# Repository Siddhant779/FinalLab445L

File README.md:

# ECE445L Final Lab
## Link to award won - Spring 2024
https://github.com/ECE445L/ECE445L-Winners
## Deliverables

The deliverables folder should contain documentation about your project as
outlined in the lab documents.

## HW

The hw folder should contain your schematic and board files for your PCB or
circuits. In labs 3-11, you will be creating schematics for your circuit
in EAGLE. A setup tutorial can be found
[here](https://www.shawnvictor.net/autodesk-eagle.html).

## SW

The sw folder should contain your application firmware and software written for
the lab. The sw/inc folder contains firmware drivers written for you by
Professor Valvano. Feel free to write your own (in fact, in some labs, you may
be required to write your own).

You can place any other source files in the sw/ folder. TAs will look at the
files you create and/or modify for software quality and for running your
project.

## Resources

A couple files are provided in the Resources folder so you don't have to keep
searching for that one TI document. Some of them are immediately useful, like
the TM4C datasheet. Others may be useful for your final project, like the
TM4C_System_Design_Guidelines page.

## Git and Github

We will extensively use Git and Github for managing lab projects. This makes it
easier for TAs to grade and help debug the project by allowing the students to
see commit histories, maintain a common project structure, collaborate with
partners, merge different codebases, and to debug work.

Two common ways of using Git and Github are [Github Desktop](https://desktop.github.com/) and the [command line](https://git-scm.com/downloads). [Tutorials](https://dev.to/mollynem/git-github--workflow-fundamentals-5496) are also abundant on the net for you to peruse. We've provided a cheatsheet for git in the Resources folder.

It is highly recommended to make the most out of Git, even if you've never used
it before. Version control will save you a lot of suffering, and tools like Git
or SVN are ubiquitous in the industry.

## Lab Report

Following the lab doc provided at the root of this project, the TAs request you
submit a lab report in Microsoft Word (or Pages, if you're a Mac user). Please
name it `EID_lab_LAB_NUMBER_report.pdf`. Templates are provided in the root dir.

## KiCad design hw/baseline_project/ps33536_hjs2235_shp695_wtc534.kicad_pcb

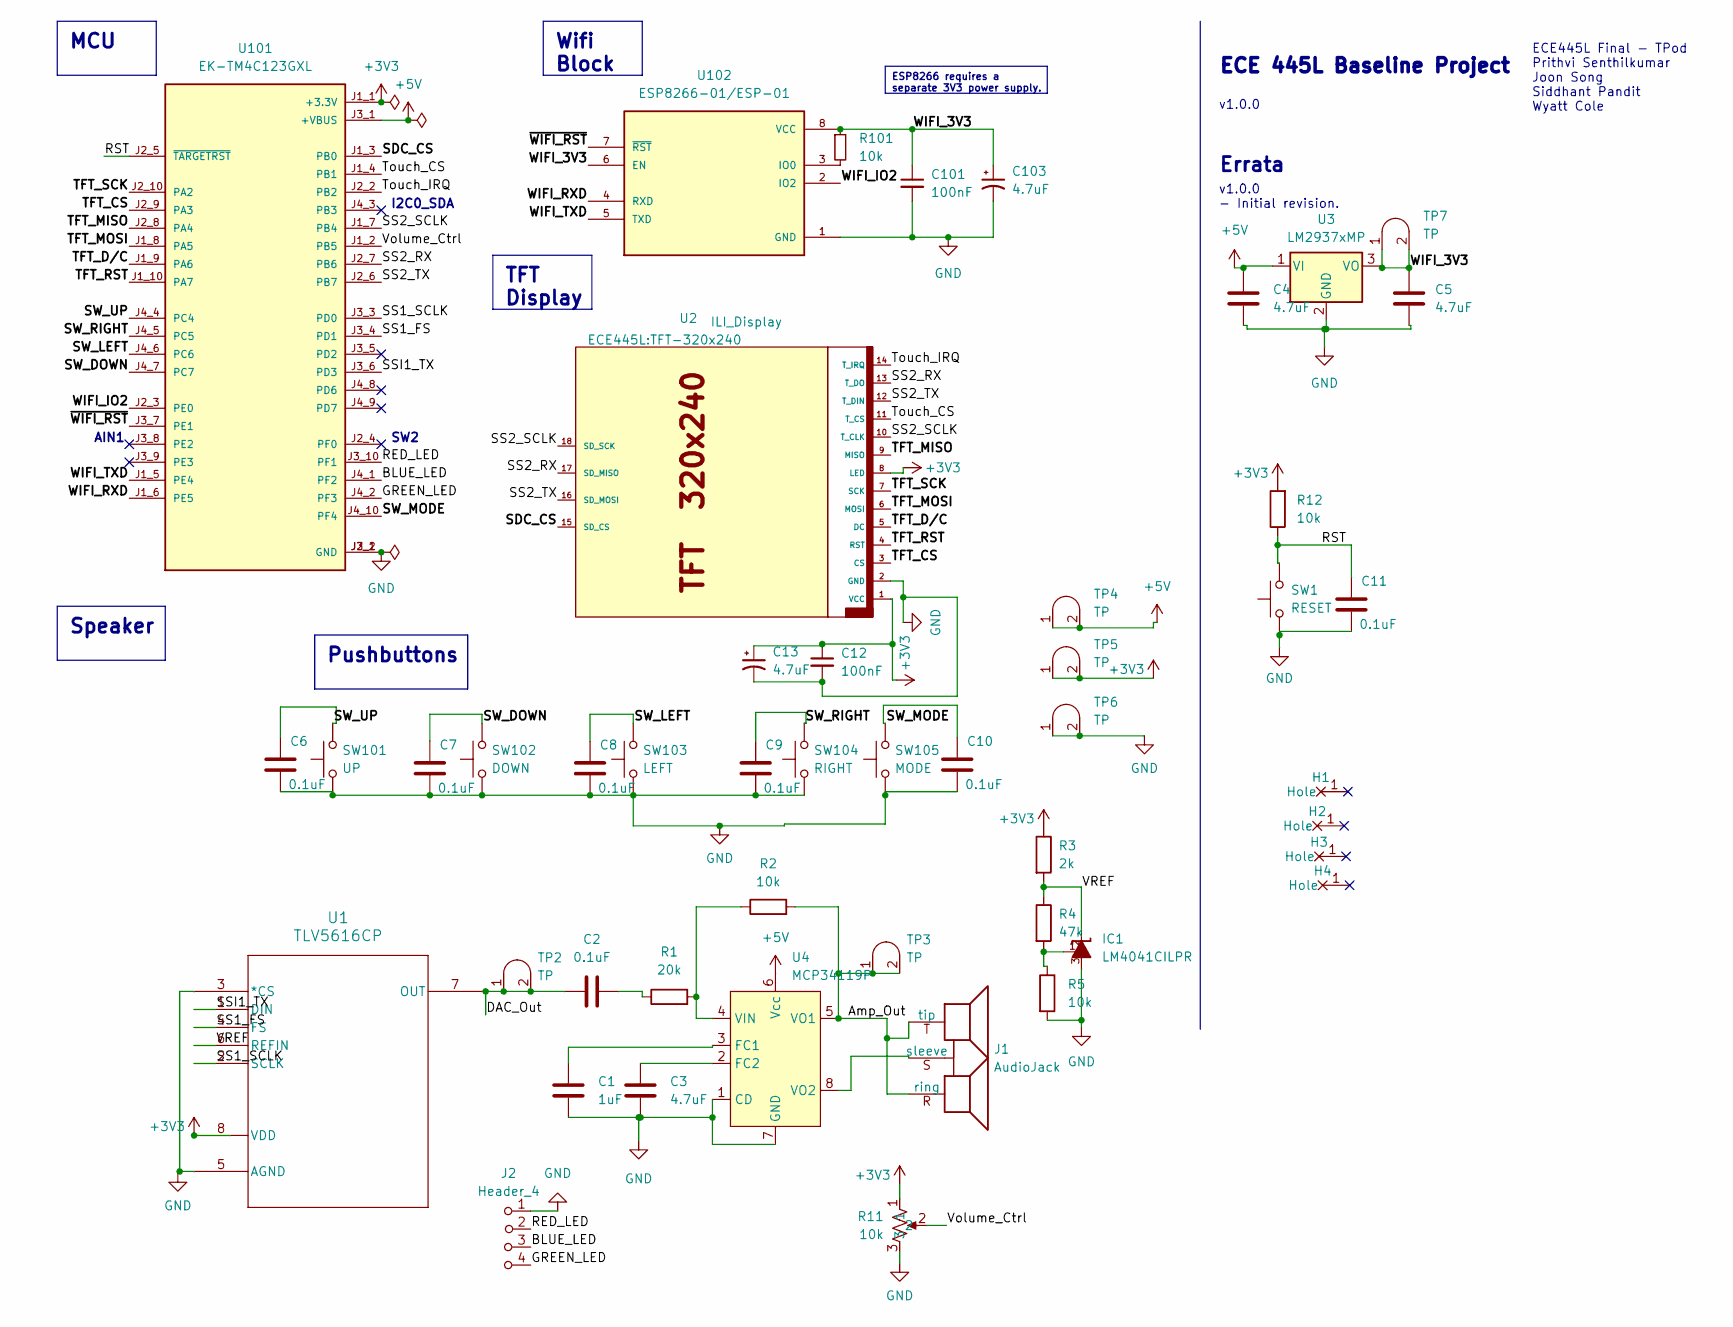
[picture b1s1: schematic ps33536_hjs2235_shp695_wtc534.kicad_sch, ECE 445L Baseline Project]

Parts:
C1: 1uF; C_Axial_200mil
C2, C6, C7, C8, C9, C10, C11: 0.1uF; C_Axial_200mil
C3, C4, C5: 4.7uF; C_Axial_200mil
C12, C101: 100nF; C_Axial_200mil
C13, C103: 4.7uF; CP_Radial_Tantal200mil
H1, H2, H3, H4: MountingHole_4_40
IC1: LM4041CILPR; ti_LM4041CILPR
J1: AudioJack; Jack_3.5mm_CUI_SJ1-3523N_Horizontal
J2: Header_4; PinHeader_1x04_P2.54mm_Vertical
R1: 20k; R_Axial_DIN0207_L6.3mm_D2.5mm_P10.16mm_Horizontal
R2, R5, R12, R101: 10k; R_Axial_DIN0207_L6.3mm_D2.5mm_P10.16mm_Horizontal
R3: 2k; R_Axial_DIN0207_L6.3mm_D2.5mm_P10.16mm_Horizontal
R4: 47k; R_Axial_DIN0207_L6.3mm_D2.5mm_P10.16mm_Horizontal
R11: 10k; Potentiometer
SW1: RESET; SW_PUSH_6mm
SW101: UP; SW_PUSH_6mm
SW102: DOWN; SW_PUSH_6mm
SW103: LEFT; SW_PUSH_6mm
SW104: RIGHT; SW_PUSH_6mm
SW105: MODE; SW_PUSH_6mm
TP2, TP3, TP4, TP5, TP6, TP7: TP; Testpoint_1x02_P2.54mm
U1: TLV5616CP; ul_TLV5616CP
U2: ILI_Display; TFT-320x240
U3: LM2937xMP; LM2937
U4: MCP34119P; DIP-8_W7.62mm_LongPads
U101: EK-TM4C123GXL; ti_EKTM4C123GXL
U102: ESP8266-01/ESP-01; ai_thinker_ESP8266_01

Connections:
+3V3: C12.1, C13.1, R3.1, R11.1, R12.2, TP5.1 (A), TP5.2 (B), U1.8 (VDD), U2.1 (VCC), U2.8 (LED), U101.J1_1 (+3.3V)
+5V: C4.1, TP4.1 (A), TP4.2 (B), U3.1 (VI), U4.6 (Vcc), U101.J3_1 (+VBUS)
/Amp_Out: J1.R (ring), J1.T (tip), R2.2, TP3.1 (A), TP3.2 (B), U4.5 (VO1)
/BLUE_LED: J2.3 (C), U101.J4_1 (PF2)
/DAC_Out: C2.2, TP2.1 (A), TP2.2 (B), U1.7 (OUT)
/GREEN_LED: J2.4 (C), U101.J4_2 (PF3)
/RED_LED: J2.2 (B), U101.J3_10 (PF1)
/RST: C11.1, R12.1, SW1.2, U101.J2_5 (~TARGETRST)
/SDC_CS: U2.15 (SD_CS), U101.J1_3 (PB0)
/SS1_FS: U1.4 (FS), U101.J3_4 (PD1)
/SS1_SCLK: U1.2 (SCLK), U101.J3_3 (PD0)
/SS2_RX: U2.13 (T_DO), U2.17 (SD_MISO), U101.J2_7 (PB6)
/SS2_SCLK: U2.10 (T_CLK), U2.18 (SD_SCK), U101.J1_7 (PB4)
/SS2_TX: U2.12 (T_DIN), U2.16 (SD_MOSI), U101.J2_6 (PB7)
/SSI1_TX: U1.1 (DIN), U101.J3_6 (PD3)
/SW_DOWN: C7.1, SW102.2, U101.J4_7 (PC7)
/SW_LEFT: C8.1, SW103.2, U101.J4_6 (PC6)
/SW_MODE: C10.1, SW105.2, U101.J4_10 (PF4)
/SW_RIGHT: C9.1, SW104.2, U101.J4_5 (PC5)
/SW_UP: C6.1, SW101.2, U101.J4_4 (PC4)
/TFT_CS: U2.3 (CS), U101.J2_9 (PA3)
/TFT_D/C: U2.5 (DC), U101.J1_9 (PA6)
/TFT_MISO: U2.9 (MISO), U101.J2_8 (PA4)
/TFT_MOSI: U2.6 (MOSI), U101.J1_8 (PA5)
/TFT_RST: U2.4 (RST), U101.J1_10 (PA7)
/TFT_SCK: U2.7 (SCK), U101.J2_10 (PA2)
/Touch_CS: U2.11 (T_CS), U101.J1_4 (PB1)
/Touch_IRQ: U2.14 (T_IRQ), U101.J2_2 (PB2)
/VREF: IC1.2, R3.2, R4.1, U1.6 (REFIN)
/Volume_Ctrl: R11.2, U101.J1_2 (PB5)
/WIFI_3V3: C5.1, C101.1, C103.1, R101.1, TP7.1 (A), TP7.2 (B), U3.3 (VO), U102.6 (EN), U102.8 (VCC)
/WIFI_IO2: U101.J2_3 (PE0), U102.2 (IO2)
/WIFI_RXD: U101.J1_6 (PE5), U102.4 (RXD)
/WIFI_TXD: U101.J1_5 (PE4), U102.5 (TXD)
/~WIFI_RST: U101.J3_7 (PE1), U102.7 (~RST)
GND: C1.2, C3.2, C4.2, C5.2, C6.2, C7.2, C8.2, C9.2, C10.2, C11.2, C12.2, C13.2, C101.2, C103.2, IC1.3, J2.1 (A), R5.2, R11.3, SW1.1, SW101.1, SW102.1, SW103.1, SW104.1, SW105.1, TP6.1 (A), TP6.2 (B), U1.3 (*CS), U1.5 (AGND), U2.2 (GND), U3.2 (GND), U4.1 (CD), U4.7 (GND), U101.J2_1 (GND), U101.J3_2 (GND), U102.1 (GND)
unnamed: C2.1, R1.1
unnamed: IC1.1, R4.2, R5.1
unnamed: J1.S (sleeve), U4.8 (VO2)
unnamed: C1.1, U4.3 (FC1)
unnamed: C3.1, U4.2 (FC2)
unnamed: R1.2, R2.1, U4.4 (VIN)
unnamed: R101.2, U102.3 (IO0)

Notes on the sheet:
MCU
ESP8266 requires a separate 3V3 power supply.
Speaker
Pushbuttons
TFT Display
Wifi Block
v1.0.0 - Initial revision.
AIN1
ECE 445L Baseline Project
v1.0.0
Errata
ECE445L Final - TPod Prithvi Senthilkumar Joon Song Siddhant Pandit Wyatt Cole
I2C0_SDA
SW2

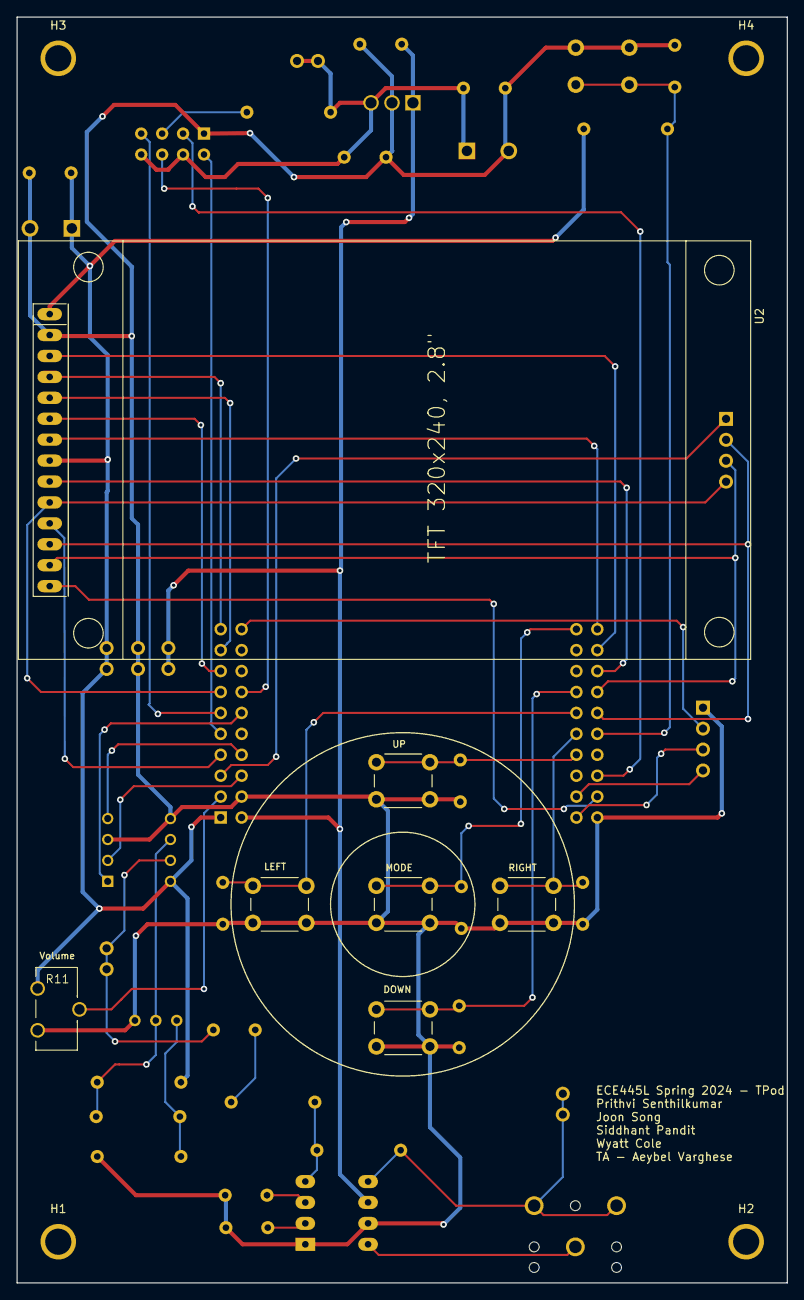
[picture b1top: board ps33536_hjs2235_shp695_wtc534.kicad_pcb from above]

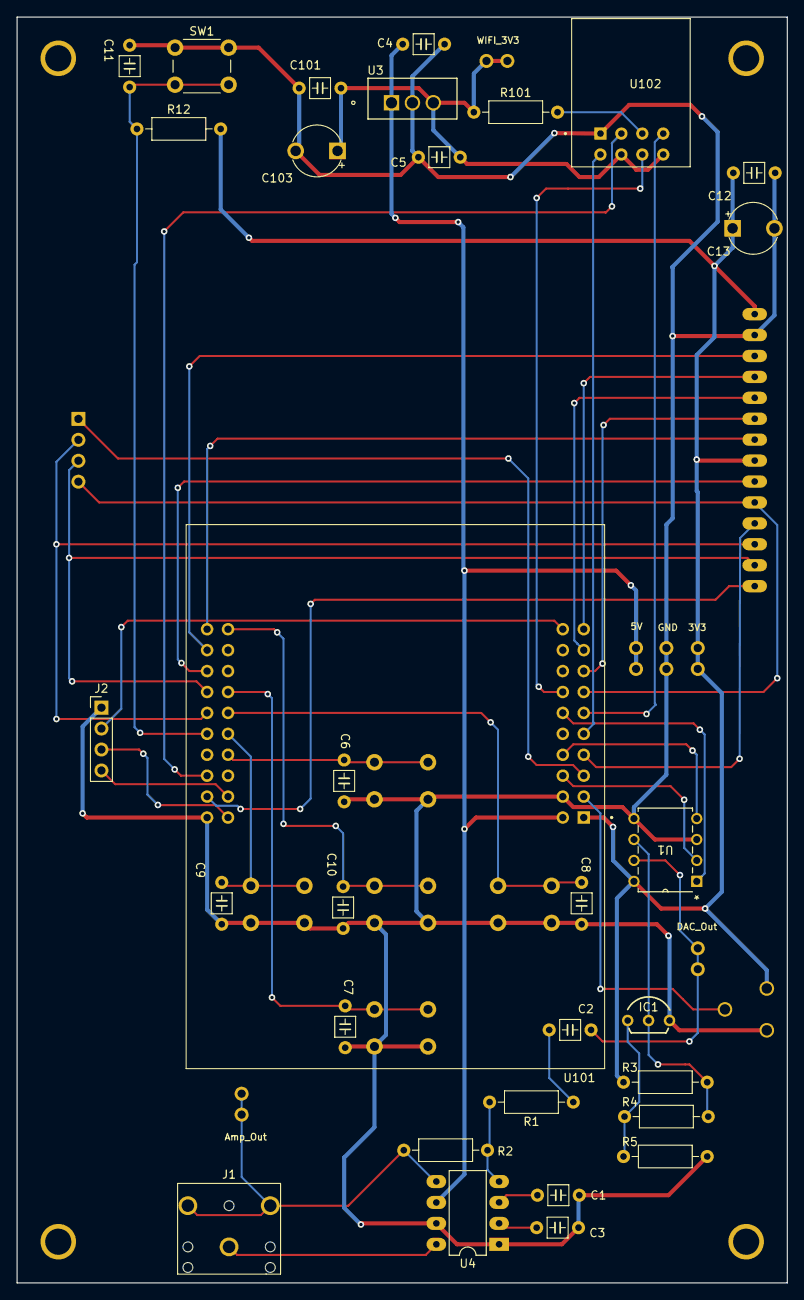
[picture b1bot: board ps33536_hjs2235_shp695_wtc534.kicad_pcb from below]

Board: 2 copper layers, 93.5 x 153.7 mm, 48 parts (37 on the bottom side), 43 nets.

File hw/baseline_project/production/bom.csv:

Designator,Footprint,Quantity,Value,LCSC Part #
C1,C_Axial_200mil,1,1uF,
"C10, C11, C2, C6, C7, C8, C9",C_Axial_200mil,7,0.1uF,
"C101, C12",C_Axial_200mil,2,100nF,
"C103, C13",CP_Radial_Tantal200mil,2,4.7uF,
"C3, C4, C5",C_Axial_200mil,3,4.7uF,
"H1, H2, H3, H4",MountingHole_4_40,4,~,
IC1,ti_LM4041CILPR,1,LM4041CILPR,
J1,Jack_3.5mm_CUI_SJ1-3523N_Horizontal,1,AudioJack,
J2,PinHeader_1x04_P2.54mm_Vertical,1,Header_4,
R1,R_Axial_DIN0207_L6.3mm_D2.5mm_P10.16mm_Horizontal,1,20k,
"R101, R12, R2, R5",R_Axial_DIN0207_L6.3mm_D2.5mm_P10.16mm_Horizontal,4,10k,
R11,Potentiometer,1,10k,
R3,R_Axial_DIN0207_L6.3mm_D2.5mm_P10.16mm_Horizontal,1,2k,
R4,R_Axial_DIN0207_L6.3mm_D2.5mm_P10.16mm_Horizontal,1,47k,
SW1,SW_PUSH_6mm,1,RESET,
SW101,SW_PUSH_6mm,1,UP,
SW102,SW_PUSH_6mm,1,DOWN,
SW103,SW_PUSH_6mm,1,LEFT,
SW104,SW_PUSH_6mm,1,RIGHT,
SW105,SW_PUSH_6mm,1,MODE,
"TP2, TP3, TP4, TP5, TP6, TP7",Testpoint_1x02_P2.54mm,6,TP,
U1,ul_TLV5616CP,1,TLV5616CP,
U101,ti_EKTM4C123GXL,1,EK-TM4C123GXL,
U102,ai_thinker_ESP8266_01,1,ESP8266-01/ESP-01,
U2,TFT-320x240,1,ILI_Display,
U3,LM2937,1,LM2937xMP,
U4,DIP-8_W7.62mm_LongPads,1,MCP34119P,

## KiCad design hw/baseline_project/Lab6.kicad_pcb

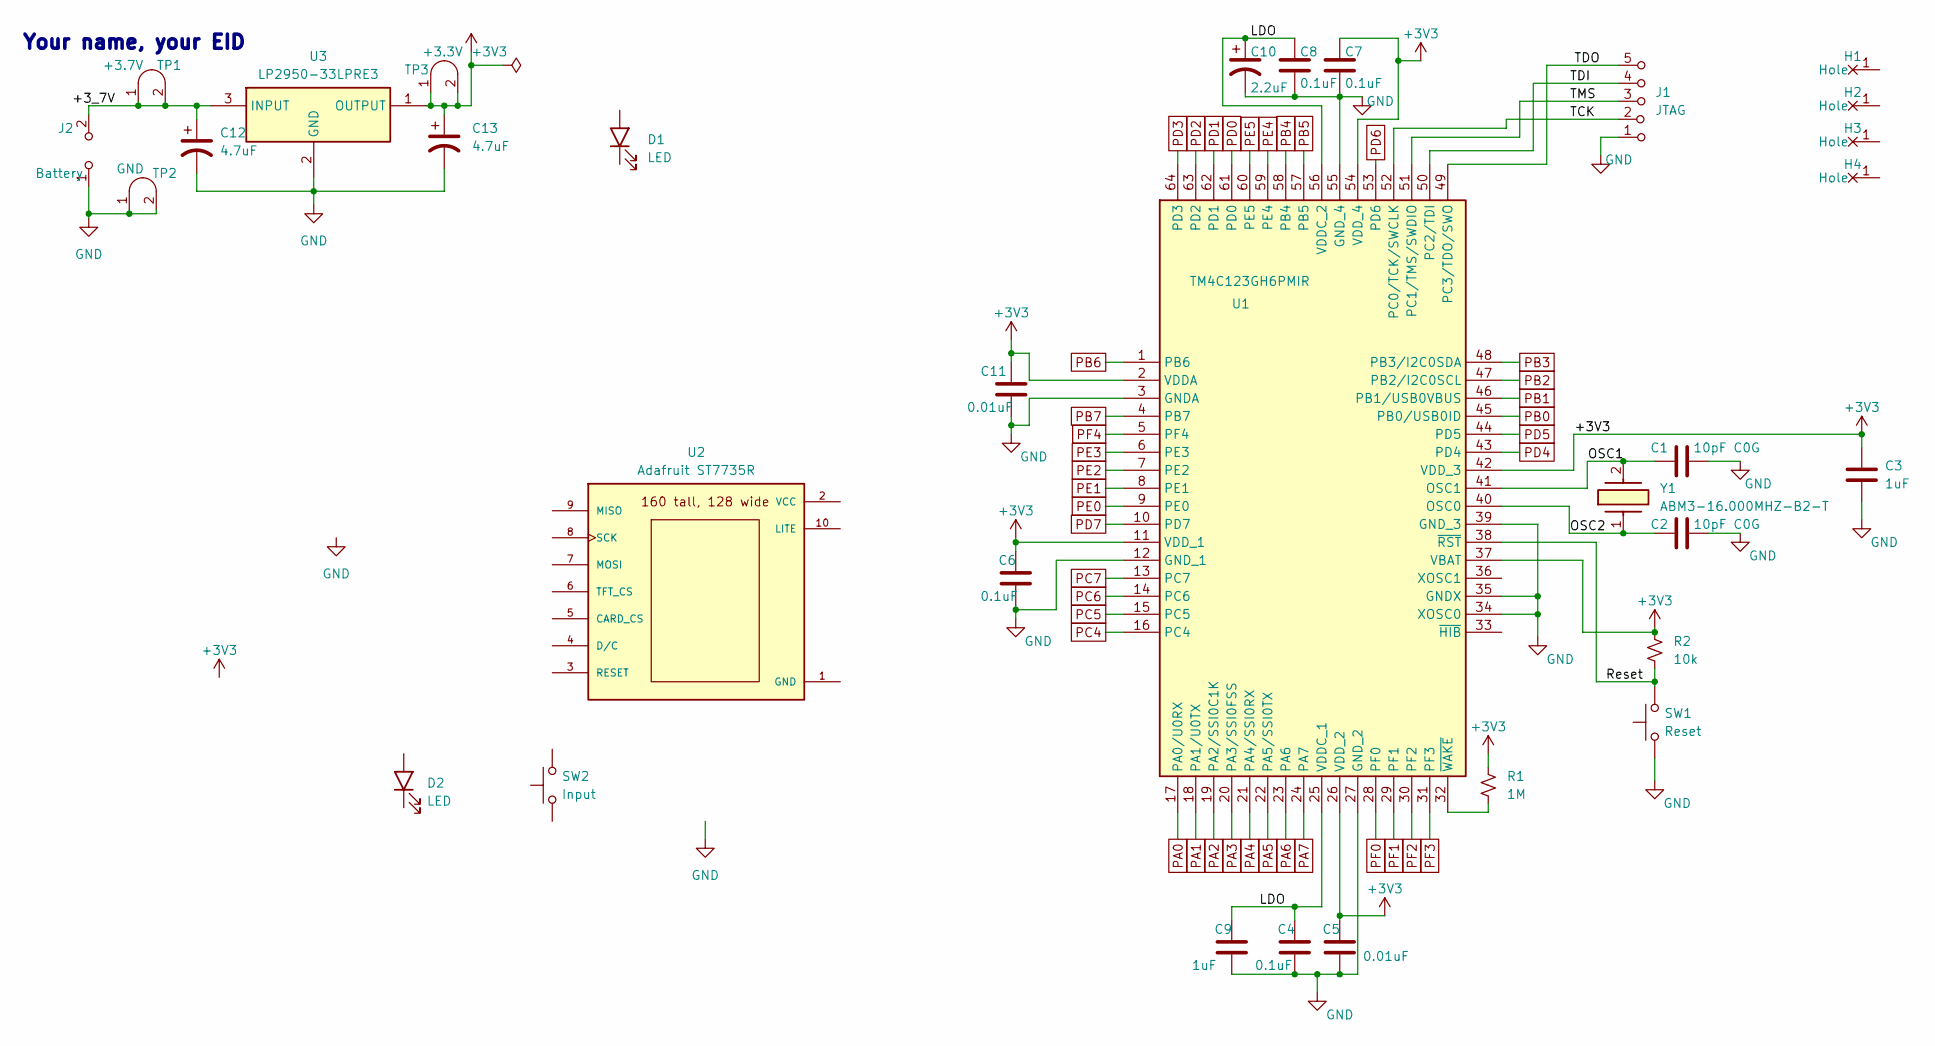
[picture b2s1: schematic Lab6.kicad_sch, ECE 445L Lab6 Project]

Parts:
C1, C2: 10pF C0G; C_Axial_200mil
C3, C9: 1uF; C_Axial_200mil
C4, C6, C7, C8: 0.1uF; C_Axial_200mil
C5, C11: 0.01uF; C_Axial_200mil
C10: 2.2uF; CP_Radial_Tantal200mil
C12, C13: 4.7uF; CP_Radial_Tantal200mil
D1, D2: LED; LED_D5.0mm
H1, H2, H3, H4: MountingHole_4_40
J1: JTAG; PinHeader_1x05_P2.54mm_Vertical
J2: Battery; PinHeader_1x02_P2.54mm_Vertical
R1: 1M; R_Axial_DIN0204_L3.6mm_D1.6mm_P7.62mm_Horizontal
R2: 10k; R_Axial_DIN0204_L3.6mm_D1.6mm_P7.62mm_Horizontal
SW1: Reset; SW_PUSH_6mm
SW2: Input; SW_PUSH_6mm
TP1: +3.7V; Testpoint_1x02_P2.54mm
TP2: GND; Testpoint_1x02_P2.54mm
TP3: +3.3V; Testpoint_1x02_P2.54mm
U1: TM4C123GH6PMIR; QFP50P1200X1200X160-64N; Mouser Part Number 595-TM4C123GH6PMIR
U2: Adafruit ST7735R; adafruit_st7735r2
U3: LP2950-33LPRE3; TL431CLPM; Mouser Part Number 595-LP2950-33LPRE3
Y1: ABM3-16.000MHZ-B2-T; ABM3; Mouser Part Number 815-ABM3-16-B2-T

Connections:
+3V3: C3.1, C5.1, C6.1, C7.1, C11.1, C13.1, R1.1, R2.1, TP3.1 (A), TP3.2 (B), U1.2 (VDDA), U1.11 (VDD_1), U1.26 (VDD_2), U1.37 (VBAT), U1.42 (VDD_3), U1.54 (VDD_4), U3.1 (OUTPUT)
/+3_7V: C12.1, J2.2 (B), TP1.1 (A), TP1.2 (B), U3.3 (INPUT)
/LDO: C4.1, C8.1, C9.1, C10.1, U1.25 (VDDC_1), U1.56 (VDDC_2)
/OSC1: C1.1, U1.41 (OSC1), Y1.2
/OSC2: C2.1, U1.40 (OSC0), Y1.1
/Reset: R2.2, SW1.2, U1.38 (~RST)
/TCK: J1.2 (B), U1.52 (PC0/TCK/SWCLK)
/TDI: J1.4 (C), U1.50 (PC2/TDI)
/TDO: J1.5 (C), U1.49 (PC3/TDO/SWO)
/TMS: J1.3 (C), U1.51 (PC1/TMS/SWDIO)
GND: C1.2, C2.2, C3.2, C4.2, C5.2, C6.2, C7.2, C8.2, C9.2, C10.2, C11.2, C12.2, C13.2, J1.1 (A), J2.1 (A), SW1.1, TP2.1 (A), TP2.2 (B), U1.3 (GNDA), U1.12 (GND_1), U1.27 (GND_2), U1.34 (XOSC0), U1.35 (GNDX), U1.39 (GND_3), U1.55 (GND_4), U3.2 (GND)
unnamed: R1.2, U1.32 (~WAKE)
PA0: U1.17 (PA0/U0RX)
PA1: U1.18 (PA1/U0TX)
PA2: U1.19 (PA2/SSI0C1K)
PA3: U1.20 (PA3/SSI0FSS)
PA4: U1.21 (PA4/SSI0RX)
PA5: U1.22 (PA5/SSI0TX)
PA6: U1.23 (PA6)
PA7: U1.24 (PA7)
PB0: U1.45 (PB0/USB0ID)
PB1: U1.46 (PB1/USB0VBUS)
PB2: U1.47 (PB2/I2C0SCL)
PB3: U1.48 (PB3/I2C0SDA)
PB4: U1.58 (PB4)
PB5: U1.57 (PB5)
PB6: U1.1 (PB6)
PB7: U1.4 (PB7)
PC4: U1.16 (PC4)
PC5: U1.15 (PC5)
PC6: U1.14 (PC6)
PC7: U1.13 (PC7)
PD0: U1.61 (PD0)
PD1: U1.62 (PD1)
PD2: U1.63 (PD2)
PD3: U1.64 (PD3)
PD4: U1.43 (PD4)
PD5: U1.44 (PD5)
PD6: U1.53 (PD6)
PD7: U1.10 (PD7)
PE0: U1.9 (PE0)
PE1: U1.8 (PE1)
PE2: U1.7 (PE2)
PE3: U1.6 (PE3)
PE4: U1.59 (PE4)
PE5: U1.60 (PE5)
PF0: U1.28 (PF0)
PF1: U1.29 (PF1)
PF2: U1.30 (PF2)
PF3: U1.31 (PF3)
PF4: U1.5 (PF4)

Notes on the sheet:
Your name, your EID

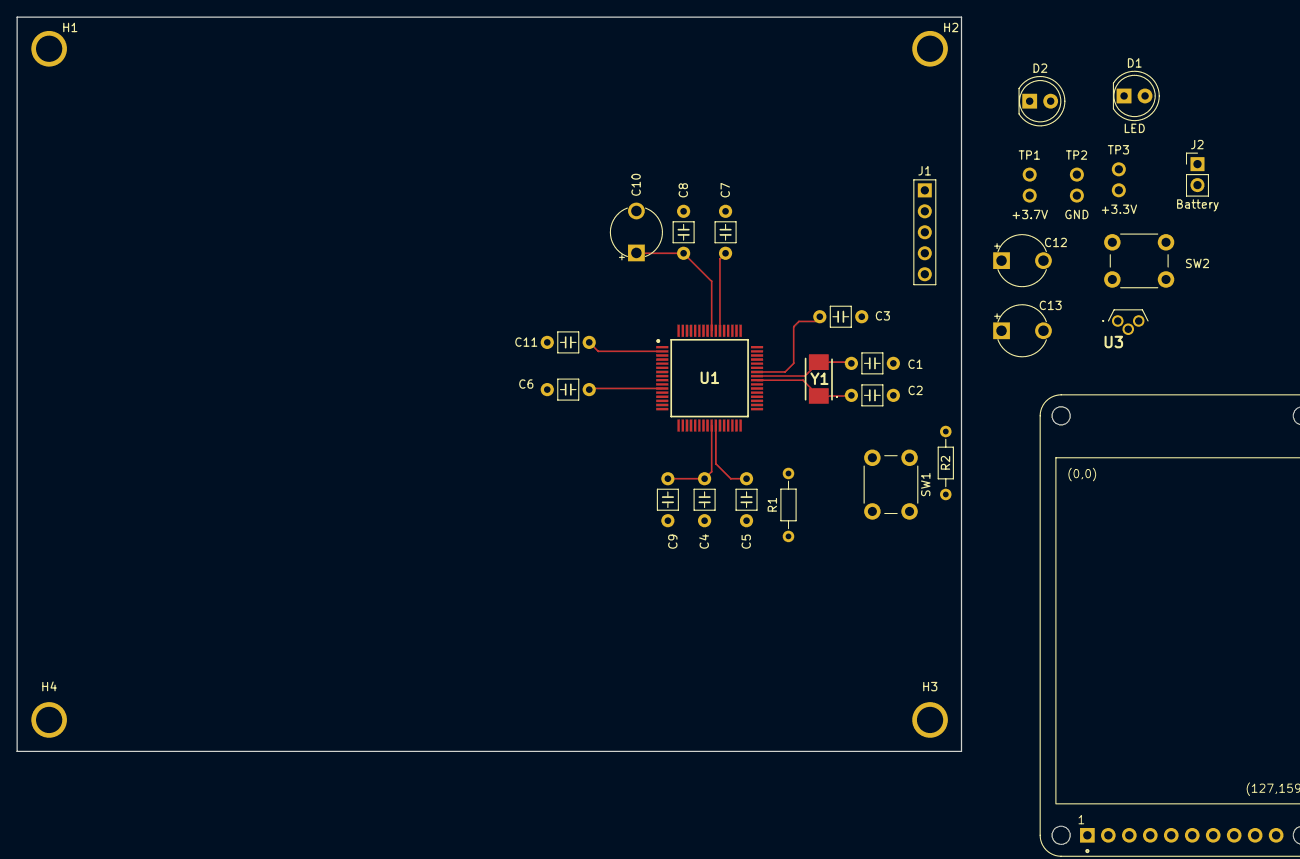
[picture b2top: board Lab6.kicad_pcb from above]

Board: 2 copper layers, 114.4 x 88.9 mm, 32 parts (0 on the bottom side), 12 nets.

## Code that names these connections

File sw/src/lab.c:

/**
 * @file        lab.c
 * @author      your name (your_email@doman.com), Jonathan Valvano, Matthew Yu
 *              <TA NAME and LAB SECTION # HERE>
 * @brief       An empty main file for running your lab.
 * @version     0.1.0
 * @date        2022-10-08 <REPLACE WITH DATE OF LAST REVISION>
 * @copyright   Copyright (c) 2022
 * @note        Potential Pinouts:
 *                  Backlight (pin 10) connected to +3.3 V
 *                  MISO (pin 9) unconnected
 *                  SCK (pin 8) connected to PA2 (SSI0Clk)
 *                  MOSI (pin 7) connected to PA5 (SSI0Tx)
 *                  TFT_CS (pin 6) connected to PA3 (SSI0Fss)
 *                  CARD_CS (pin 5) unconnected
 *                  Data/Command (pin 4) connected to PA6 (GPIO)
 *                  RESET (pin 3) connected to PA7 (GPIO)
 *                  VCC (pin 2) connected to +3.3 V
 *                  Gnd (pin 1) connected to ground
 *
 *                  Center of 10k-ohm potentiometer connected to PE2/AIN1
 *                  Bottom of 10k-ohm potentiometer connected to ground
 *                  Top of 10k-ohm potentiometer connected to +3.3V
 *
 *              Warning. Initial code for the RGB driver creates bright flashing
 *              lights. Remove this code and do not run if you have epilepsy.
 */
 
 
//files to include 
/*
main one 
esp base - wifi one - arduino
sockets file - send receive functions in this 
menu file - fsm 
controls file - buttons deals with that 
*/

/** File includes. */
#include <stdint.h>
#include <stdio.h>
#include <string.h>
/* Register definitions. */
#include "./inc/tm4c123gh6pm.h"
/* Clocking. */
#include "./inc/PLL.h"
/* Clock delay and interrupt control. */
#include "./inc/CortexM.h"
/* Initialization of all the pins. */
#include "./inc/Unified_Port_Init.h"
/* Talking to PC via UART. */
#include "./inc/UART.h"
/* ST7735 display. */
#include "ILI9341.h"


/* Add whatever else you need here! */
#include "Switch.h"
#include "Music.h"
#include "../lib/SD/eDisk.h"
#include "../lib/SD/ff.h"
#include "Display.h"
#include "Messages.h"
#include "FSM.h"
#include "./inc/Timer5A.h"
#include "./inc/UART5.h"
#include "./inc/esp8266_base.h"
// port b 6

/** MMAP Pin definitions. */
#define PF0   (*((volatile uint32_t *)0x40025004)) // Left Button
#define PF1   (*((volatile uint32_t *)0x40025008)) // RED LED
#define PF2   (*((volatile uint32_t *)0x40025010)) // BLUE LED
#define PF3   (*((volatile uint32_t *)0x40025020)) // GREEN LED
#define PF4   (*((volatile uint32_t *)0x40025040)) // Right Button
	
void Pause(void);
void DelayWait10ms(uint32_t n);

static FATFS g_sFatFs;
FRESULT MountFresult;


//we are going to have to map the album cover to teh sonsg - we would ahve to use 


int main(void) {
    /* Disable interrupts for initialization. */
    DisableInterrupts();

    /* Initialize clocking. */
    PLL_Init(Bus80MHz);

    /* Allow us to talk to the PC via PuTTy! Check device manager to see which
       COM serial port we are on. The baud rate is 115200 chars/s. */
    UART_Init();
    UART5_Init();
    Reset_8266();
    SetupWiFi();

    /* Initialize all ports. */
    Unified_Port_Init();
	  //SSI2_Init(4);
	//ST7735_InitR(INITR_REDTAB);     // Start up display.
    ILI9341_init();
	//setRotation(3);

    /* Start RGB flashing. WARNING! BRIGHT FLASHING COLORS. DO NOT RUN IF YOU HAVE EPILEPSY. */
    //RGBInit();
		
    /* Initialize buttons */
    switch_init();

    /* Initialize music driver */
    //SongStrIndex = 0;
    music_init();
    message_init();
		
    FSM_Init();

    /* Allows any enabled timers to begin running. */
    EnableInterrupts();
    ILI9341_fillScreen(ILI9341_WHITE);
	

    front8 = Buf2; // buffer being output to DAC
    back8 = Buf;   // buffer being written to from SDC
    Count8 = 0;
    flag8 = 0; // 1 means need data into back
    BufCount8 = 0;
    done_song = 0;
    stop_dac = 0;



    MountFresult = f_mount(&g_sFatFs, "", 0);
    if(MountFresult){
        //ILI9341_DrawString(52, 0, "f_mount error",0x03E0 , 2);
    }
    

    LoadBitmap(Songs[SongStrIndex].album_file);
    replacealbumCover(Get_State().name, false);
    load_song();
    pause_song();

    // Main while loop of system
    while(1){
        //could check if need to draw flag here. If so, Fill screen white
        //set needtoDraw in FSMController when state transitions to a new menu, like all the back button tran
        State_t current_state = Get_State();
        if (get_clear_flag()){
            ILI9341_fillScreen(ILI9341_WHITE);
            replacealbumCover(current_state.name, true);
            set_clear_flag(0);
        }
        switch(current_state.name){
            case menu_mus:
            case menu_msg:
            case menu_play:
            case menu_pl:
            case menu_fa:
            case menu_re:
                drawMainMenu(current_state.name);
                break;
            case song1:
            case song2:
            case song3:
            case song4:
            case song5:
            case song6:
            case song7:
            case mus_pl:
            case mus_fa:
            case mus_re:
            case mus_ba:
                drawMusicPage(current_state.name);
                break;
            case np_pl:
            case np_fa:
            case np_re:
            case np_ba:
                drawNowPlayingPage(current_state.name);
                break;
            case msg_bck:
            case msg_key:
                display_keys();
                break;
        }
        // other tasks
    }
}

/** Function Implementations. */
void DelayWait10ms(uint32_t n) {
    uint32_t volatile time;
    while (n){
        time = 727240 * 2 / 91;  // 10msec
        while (time){
            --time;
        }
        --n;
    }
}

void Pause(void) {
    while (PF4 == 0x00) {
        DelayWait10ms(10);
    }
    while (PF4 == 0x10) {
        DelayWait10ms(10);
    }
}

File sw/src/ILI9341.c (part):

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 *                       T_IRQ: --
 *                        T_DO: -
 *                       T_DIN: -
 *  SD_SCK: PB4           T_CS: -
 * SD_MISO: PB6          T_CLK: -
 * SD_MOSI: PB7           MISO: -
 *   SD_CS: PB0            LED: 3.3V
 *                         SCK: PA2
 *                        MOSI: PA5
 *                          DC: PA6
 *                       RESET: PA7
 *                          CS: PA3
 *                         GND: GND
 *                         VCC:  3.3V

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


#define TFT_CS                  (*((volatile uint32_t *)0x40004020))
#define TFT_CS_LOW              0           // CS normally controlled by hardware
#define TFT_CS_HIGH             0x08
#define DC                      (*((volatile uint32_t *)0x40004100))
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
    // toggle RST low to reset; CS low so it'll listen to us
    // SSI0Fss is temporarily used as GPIO
    GPIO_PORTA_DIR_R |= 0xC8;             // make PA3,6,7 out
    GPIO_PORTA_AFSEL_R &= ~0xC8;          // disable alt funct on PA3,6,7
    GPIO_PORTA_DEN_R |= 0xC8;             // enable digital I/O on PA3,6,7
                                        // configure PA3,6,7 as GPIO
    GPIO_PORTA_PCTL_R = (GPIO_PORTA_PCTL_R&0x00FF0FFF)+0x00000000;
    GPIO_PORTA_AMSEL_R &= ~0xC8;          // disable analog functionality on PA3,6,7
    //GPIOPinWrite(GPIO_PORTE_BASE, GPIO_PIN_5, GPIO_PIN_5);
    //sleep(10);
    //GPIOPinWrite(GPIO_PORTE_BASE, GPIO_PIN_5, 0);
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    Delay1ms(500);

    // initialize SSI0
    GPIO_PORTA_AFSEL_R |= 0x2C;           // enable alt funct on PA2,3,5
    GPIO_PORTA_DEN_R |= 0x2C;             // enable digital I/O on PA2,3,5
                                        // configure PA2,3,5 as SSI
    GPIO_PORTA_PCTL_R = (GPIO_PORTA_PCTL_R&0xFF0F00FF)+0x00202200;
    GPIO_PORTA_AMSEL_R &= ~0x2C;          // disable analog functionality on PA2,3,5
    SSI0_CR1_R &= ~SSI_CR1_SSE;           // disable SSI
    SSI0_CR1_R &= ~SSI_CR1_MS;            // master mode
                                        // configure for system clock/PLL baud clock source
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
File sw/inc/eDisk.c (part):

// eDisk.c
// Runs on LM4F120/TM4C123
// Use SSI0, PD7/PB0 to communicate with the SDC.
// Valvano
// March 9, 2017
// added PB0 as a choice for card CS

/* This example accompanies the books
   "Embedded Systems: Real Time Interfacing to Arm Cortex M Microcontrollers",
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 For more information about my classes, my research, and my books, see
 http://users.ece.utexas.edu/~valvano/
 */
// there is a #define below to select SDC CS as PD7 or PB0

// Backlight (pin 10) connected to +3.3 V
// MISO (pin 9) connected to PA4 (SSI0Rx)
// SCK (pin 8) connected to PA2 (SSI0Clk)
// MOSI (pin 7) connected to PA5 (SSI0Tx)
// TFT_CS (pin 6) connected to PA3 (SSI0Fss) <- GPIO high to disable TFT
// CARD_CS (pin 5) connected to PD7/PB0 GPIO output 
// Data/Command (pin 4) connected to PA6 (GPIO)<- GPIO low not using TFT
// RESET (pin 3) connected to PA7 (GPIO)<- GPIO high to disable TFT
// VCC (pin 2) connected to +3.3 V
// Gnd (pin 1) connected to ground

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// Silkscreen Label (SDC side up; LCD side down) - Connection
// VCC  - +3.3 V
// GND  - Ground
// !SCL - PA2 Sclk SPI clock from microcontroller to TFT or SDC
// !SDA - PA5 MOSI SPI data from microcontroller to TFT or SDC
// DC   - PA6 TFT data/command
// RES  - PA7 TFT reset
// CS   - PA3 TFT_CS, active low to enable TFT
// *CS  - PD7/PB0 SDC_CS, active low to enable SDC
// MISO - PA4 MISO SPI data from SDC to microcontroller
// SDA  � (NC) I2C data for ADXL345 accelerometer
// SCL  � (NC) I2C clock for ADXL345 accelerometer
// SDO  � (NC) I2C alternate address for ADXL345 accelerometer
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
#define SDC_CS_PB0 1
#define SDC_CS_PD7 0
#define TFT_CS                  (*((volatile unsigned long *)0x40004020))
#define TFT_CS_LOW              0           // CS normally controlled by hardware
#define TFT_CS_HIGH             0x08

#if SDC_CS_PD7
// CS is PD7  
// to change CS to another GPIO, change SDC_CS and CS_Init
#define SDC_CS   (*((volatile unsigned long *)0x40007200)) 
#define SDC_CS_LOW       0           // CS controlled by software
#define SDC_CS_HIGH      0x80  
void CS_Init(void){ 
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}
#endif
#if SDC_CS_PB0
// CS is PB0
// to change CS to another GPIO, change SDC_CS and CS_Init
#define SDC_CS   (*((volatile unsigned long *)0x40005004)) 
#define SDC_CS_LOW       0           // CS controlled by software
#define SDC_CS_HIGH      0x01  
void CS_Init(void){ 
  SYSCTL_RCGCGPIO_R |= 0x02; // activate port B
  while((SYSCTL_PRGPIO_R&0x02)==0){};
  GPIO_PORTB_PUR_R |= 0x01;         // enable weak pullup on PB0
  GPIO_PORTB_DIR_R |= 0x01;         // make PB0 output 
  GPIO_PORTB_DR4R_R |= 0x01;        // 4mA output on outputs
  SDC_CS = SDC_CS_HIGH;
  GPIO_PORTB_PCTL_R &= ~0x0000000F;
  GPIO_PORTB_AMSEL_R &= ~0x01; // disable analog functionality on PB0
  GPIO_PORTB_DEN_R |= 0x01;    // enable digital I/O on PB0
}
#endif

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  // initialize Port A
  SYSCTL_RCGCGPIO_R |= 0x01;            // activate clock for Port A
  while((SYSCTL_PRGPIO_R&0x01) == 0){}; // allow time for clock to stabilize
  GPIO_PORTA_DIR_R |= 0x08;             // make PA3 out
  GPIO_PORTA_AFSEL_R |= 0x34;           // enable alt funct on PA2,4,5
  GPIO_PORTA_AFSEL_R &= ~0x08;          // disable alt funct on PA3
  GPIO_PORTA_DR4R_R |= 0xFC;            // 4mA drive on outputs
  GPIO_PORTA_PUR_R |= 0x3C;             // enable weak pullup on PA2,3,4,5
  GPIO_PORTA_DEN_R |= 0x3C;             // enable digital I/O on PA2,3,4,5
                                        // configure PA2,4,5 as SSI
  GPIO_PORTA_PCTL_R = (GPIO_PORTA_PCTL_R&0xFF00F0FF)+0x00220200;
                                        // configure PA3 as GPIO
  GPIO_PORTA_PCTL_R = (GPIO_PORTA_PCTL_R&0xFFFF0FFF)+0x00000000;
  GPIO_PORTA_AMSEL_R &= ~0x3C;          // disable analog functionality on PA2,3,4,5
  GPIO_PORTA_DATA_R |= 0x88;            // PA7, PA3 high (disable LCD)
  // initialize SSI0
  SYSCTL_RCGCSSI_R |= 0x01;             // activate clock for SSI0
  while((SYSCTL_PRSSI_R&0x01) == 0){};  // allow time for clock to stabilize
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#define FCLK_FAST() { SSI0_CPSR_R = (SSI0_CPSR_R&~SSI_CPSR_CPSDVSR_M)+8; }

// de-asserts the CS pin to the card
#define CS_HIGH()  SDC_CS = SDC_CS_HIGH;
// asserts the CS pin to the card
#define CS_LOW()  SDC_CS = SDC_CS_LOW;
//#define  MMC_CD    !(GPIOC_IDR & _BV(4))  /* Card detect (yes:true, no:false, default:true) */
#define  MMC_CD    1  /* Card detect (yes:true, no:false, default:true) */
#define  MMC_WP    0 /* Write protected (yes:true, no:false, default:false) */
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
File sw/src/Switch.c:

// Switch.c

#include "./inc/tm4c123gh6pm.h"
#include "Switch.h"
#include "Music.h"
#include "Messages.h"
#include "FSM.h"
	
#define PC4		(*((volatile uint32_t *) 0x40006040))	// UP
#define PC5		(*((volatile uint32_t *) 0x40006080))	// RIGHT
#define PC6		(*((volatile uint32_t *) 0x40006100))	// LEFT
#define PC7		(*((volatile uint32_t *) 0x40006200))	// DOWN
#define PF4		(*((volatile uint32_t *) 0x40025040))	// ENTER
#define PF1   (*((volatile uint32_t *) 0x40025008)) // RED LED
#define PF2   (*((volatile uint32_t *) 0x40025010)) // BLUE LED
#define PF3   (*((volatile uint32_t *) 0x40025020)) // GREEN LED


volatile static unsigned long LastUp;
volatile static unsigned long LastRight;
volatile static unsigned long LastLeft;
volatile static unsigned long LastDown;
volatile static unsigned long LastEnter;


/* Arm PC4-7 and PF4 for Interrupts */
static void SwitchArm(void) {
	// Clear and reset interrupts
	GPIO_PORTC_ICR_R = 0xF0;
	GPIO_PORTC_IM_R |= 0xF0;
	GPIO_PORTF_ICR_R = 0x10;
	GPIO_PORTF_IM_R |= 0x10;
	NVIC_PRI0_R = (NVIC_PRI0_R&0xFF00FFFF) | 0x00A00000;	// Set priority to 5 on PortC
	NVIC_PRI7_R = (NVIC_PRI7_R&0xFF00FFFF) | 0x00A00000;	// Set priority to 5 on PortF
	NVIC_EN0_R = 1<<2;						// Enable interrupt 1 (PortC) in NVIC
	NVIC_EN0_R = 1<<30;						// Enable interrupt 1 (PortF) in NVIC
}

/* Arm Timer1 for Software Debouncing */
static void Timer1Arm(void) {
	TIMER1_CTL_R = 0x00000000;		// Disable timer during setup
	TIMER1_CFG_R = 0x00000000;		// 32-bit mode
	TIMER1_TAMR_R = 0x0000001;		// One-shot mode
	TIMER1_TAILR_R = 160000;			// Period of 10ms
	TIMER1_TAPR_R = 0;						// Uses bus clock
	TIMER1_ICR_R = 0x00000001;    // Clear TIMER1A timeout flag
  TIMER1_IMR_R = 0x00000001;    // Arm timeout interrupt
  NVIC_PRI5_R = (NVIC_PRI5_R&0xFFFF00FF)|0x00008000;	// Priority 4
	NVIC_EN0_R = 1<<21;						// Enable interrupt 21 in NVIC
	TIMER1_CTL_R = 0x00000001;		// Enable TIMER1A
}

/* Initialize PC4-7 and F4 as edge-triggered interrupt inputs */
void switch_init(void) {
	GPIO_PORTC_DIR_R &= ~0xF0;		// Make PC4,5,6,7 inputs
	GPIO_PORTC_AFSEL_R &= ~0xF0;	// Disable alt function for PC4,5,6,7
	GPIO_PORTC_DEN_R |= 0xF0;			// Enable digital I/O on PC4,5,6,7
	GPIO_PORTC_AMSEL_R &= ~0xF0;	// Disable analog function for PC4,5,6,72
	GPIO_PORTC_PUR_R |= 0xF0;			// Enable pull-up on PC4,5,6,7
	GPIO_PORTC_IS_R &= ~0xF0;			// PC4,5,6,7 is edge-sensitive
	GPIO_PORTC_IBE_R |= 0xF0;			// PC4,5,6,7 is both edges
	
	// Same initializations for PF4
	GPIO_PORTF_DIR_R &= ~0x10;		
	GPIO_PORTF_AFSEL_R &= ~0x10;	
	GPIO_PORTF_DEN_R |= 0x10;			
	GPIO_PORTF_AMSEL_R &= ~0x10;	
	GPIO_PORTF_PUR_R |= 0x10;			
	GPIO_PORTF_IS_R &= ~0x10;			
	GPIO_PORTF_IBE_R |= 0x10;
	
	SwitchArm();
	SYSCTL_RCGCTIMER_R |= 0x02;		// Activate timer1
	// Set initial values of all buttons
	LastUp = PC4;
	LastRight = PC5;
	LastLeft = PC6;
	LastDown = PC7;
	LastEnter = PF4;
}

uint8_t input_encoder;
/* PortC ISR: Determine which switches were pressed/released and call function for that switch */
void GPIOPortC_Handler(void) {
	GPIO_PORTC_IM_R &= ~0xF0;			// Disarm button interrupt
	input_encoder = 0;
	// Determine which button(s) were pressed
	if(GPIO_PORTC_RIS_R&0x10)	{		// Poll PC4
		if(LastUp) {
			// Service up button
			//rewind_song();
			input_encoder = 1;
		}
	}
	if(GPIO_PORTC_RIS_R&0x20)	{		// Poll PC5
		if(LastRight) {
			// Service right button
			input_encoder = 2;
		}
	}
	if(GPIO_PORTC_RIS_R&0x40)	{		// Poll PC6
		if(LastLeft) {
			// Service left button
//			if(is_playing()) pause_song();
//			else unpause_song();
			input_encoder = 3;
		}
	}
	if(GPIO_PORTC_RIS_R&0x80)	{		// Poll PC7
		if(LastDown) {
			// Service down button
			input_encoder = 4;
		}
	}
	if (input_encoder != 0){
		FSM_Controller(input_encoder);
	}
	Timer1Arm();
}

/* PortF ISR: Determine which switches were pressed/released and call function for that switch */
void GPIOPortF_Handler(void) {
	GPIO_PORTF_IM_R &= ~0x10;			// Disarm button interrupt
	if(LastEnter) {
		// Service enter button
		input_encoder = 5;
		FSM_Controller(input_encoder);
	}
	Timer1Arm();
}

uint8_t get_input(void){
	return input_encoder;
}

/* Timer1A ISR: Save input values after debouncing */
void Timer1A_Handler(void) {
	// Debouncing is complete
	TIMER1_IMR_R = 0x00000000;	// Disarm interrupt
	// Save all switch values 
	LastUp = PC4;
	LastRight = PC5;
	LastLeft = PC6;
	LastDown = PC7;
	LastEnter = PF4;
	SwitchArm();	// Clear flags and rearm interrupts
}

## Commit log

2024-03-08 add deadline
2024-03-19 schematic
2024-03-22 slight edit schematic
2024-03-23 starter keil file
2024-03-26 Play short wav file; temporary functionality
2024-03-26 schematic done, pcb design
2024-03-27 placement ST7735 board
2024-03-27 Filling out Switch functions; still needs work
2024-03-28 routed ST7735
2024-03-28 Edge-Triggered Interrupts on PC4,5,6,7 and PF4
2024-03-28 Defined music driver
2024-03-29 Music driver
2024-03-29 Minor fixes to music driver
2024-03-29 before changing display
2024-03-29 so far so good new display pcb
2024-03-29 pcb done
2024-03-29 pcb and lab 7 report done
2024-04-02 final pcb submission
2024-04-02 ESP-Socket baseline
2024-04-02 Baseline socket
2024-04-05 lab 8 doc
2024-04-09 Volume control
2024-04-09 ESP2Server, no support for TM4C yet
2024-04-17 most Display driver functions are finished - need to work on drawChar and drawString
2024-04-17 basic format for SD Card
2024-04-17 changed pinnings
2024-04-17 added init for SD card
2024-04-17 moved SD files to lib
2024-04-17 RTOS SD implementation without OS
2024-04-18 finished display
2024-04-19 working on SD card - changed init and tried implementing it
2024-04-20 changed some things for SD card
2024-04-23 playing music from SD card works
2024-04-23 added text color to functions for display
2024-04-23 fixed colors; added function for changing bg color
2024-04-23 output keyboard
2024-04-23 updated new ILI colors
2024-04-23 can move around keyboard, need to fix x/y
2024-04-23 finished initial main menu and now playing page
2024-04-23 more keyboard progress
2024-04-23 keyboard done, needs rearrange
2024-04-23 updated all the pages and display functions
2024-04-24 moved Pages to display; fixed warning in eDisk
2024-04-24 Reading Bitmap
2024-04-24 can display message history
2024-04-24 images work from SD card
2024-04-24 fsm initial changes
2024-04-24 still working on fsm
2024-04-24 removed files for space
2024-04-24 fixed out of space error
2024-04-24 added FSM init
2024-04-24 removed flickering
2024-04-24 can navigate menu
2024-04-24 fixed msg menu
2024-04-24 images work - need to chagne size; music works need to improove - added esp stuff and deleted files
2024-04-24 changed struct:
2024-04-25 Working rewind/fast-forward
2024-04-25 More WiFi merge conflict issues
2024-04-25 basic wifi
2024-04-25 Final TM4C2SERVER
2024-04-25 Bug fixes
2024-04-25 messaging mostly works
2024-04-25 screen messages bug
2024-04-25 Added songs
2024-04-25 Uncommented Inits
2024-04-25 Removed Bad Song
2024-04-26 first part of final report
2024-04-26 last report done :)

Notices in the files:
sw/inc/eDisk.c:
ISBN: 978-1463590154, Jonathan Valvano, copyright (c) 2017
"Embedded Systems: Real-Time Operating Systems for ARM Cortex-M Microcontrollers",
ISBN: 978-1466468863, Jonathan Valvano, copyright (c) 2017
Copyright 2017 by Jonathan W. Valvano, valvano@mail.utexas.edu
